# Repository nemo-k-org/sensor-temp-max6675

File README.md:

# Nemo-K temperature sensor for type K thermocouple gauge

## Overview

This is Nemo-K board for ESP-01 and type K thermocouple temperature gauge. The board contains [MAX6675](https://www.analog.com/en/products/max6675.html)
analog-to-digital converter.

Because of its measuring range (0°C to +1024°C) MAX6675 and type K gauge is an ideal setup for measuring components
which may become extremely hot. In boat environment the engine exhaust pipes are typical monitoring target requiring
this type of scale.

The board is designed to be used with ESP-01 microcontroller running Nemo-K firmware.

## Content

The repository contains schematics and PCB in KiCad 8.0 format. The footprint properties contains LCSC part numbers
used by [JLCPBC.com](https://jlcpcb.com). If present, the `sensor-temp-max6675/production/` contains all necessary
files to order boards from JLCPCB. The production files can be easily re-created using
[KiCad Fabrication Toolkit](https://github.com/bennymeg/Fabrication-Toolkit).

The Nemo-K project is not affiliated or sponsored by JLCPCB. The project does not endorse JLCPCB.

## Changelog

* At the moment there is no field tested versions.

## Copyright and License

The license and copyright can be found in the file `LICENSE`.

The license and copyright cover only the schematic diagram and the PCB design. It does not cover footprints and other
embedded elements or technical documentation which may or may not be covered by their own licenses.

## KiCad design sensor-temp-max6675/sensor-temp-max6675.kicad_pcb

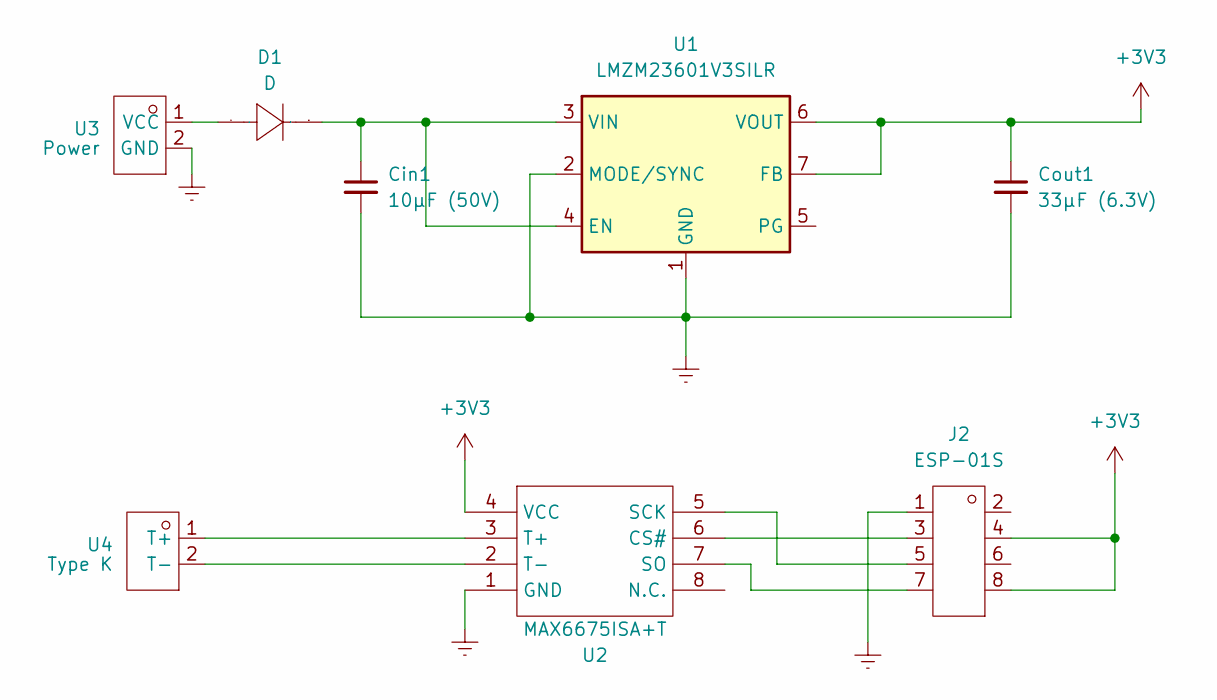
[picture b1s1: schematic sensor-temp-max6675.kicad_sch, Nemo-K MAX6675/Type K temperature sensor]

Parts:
Cin1: 10μF (50V); C_1210_3225Metric; LCSC C2918502
Cout1: 33μF (6.3V); C_1210_3225Metric; Mfg Part C3225X5R1A336MT0A0E; LCSC C531418
D1: D; SOD-323_L1.7-W1.3-LS2.5-RD; Manufacturer Part S7116-300A; LCSC Part Name S7116-300A
J2: ESP-01S; HDR-SMD_8P-P2.54-V-F-R2-C4-S7.1; Mfg Part PM254-2-04-S-8.5; LCSC C3975149
U1: LMZM23601V3SILR; Texas_SIL0010A_MicroSiP-10-1EP_3.8x3mm_P0.6mm_EP0.7x2.9mm_T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; MPN LMZM23601SILR; LCSC C2864948
U2: MAX6675ISA+T; SOIC-8_L5.0-W4.0-P1.27-LS6.0-BL; Manufacturer Part MAX6675ISA+T; LCSC Part Name MAX6675ISA
U3: Power; CONN-TH_MX127S-3.81-02P-GN01-CU-Y-A; Manufacturer Part MX127S-3.81-02P-GN01-Cu-Y-A; LCSC Part Name 1x2P 3.81mm 直插 排数:1 每排P数:2
U4: Type K; CONN-TH_2P-P7.62_KEFA_KF7.62-2P; Manufacturer Part KF7.62-2P(green); LCSC Part Name KF7.62-2P(green) 绿色尼龙环保

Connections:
+3V3: Cout1.1, J2.4 (Ch_PD), J2.8 (+3V3), U1.6 (VOUT), U1.7 (FB), U2.4 (VCC)
Earth: Cin1.2, Cout1.2, J2.1 (Earth), U1.1 (GND), U1.2 (MODE/SYNC), U1.11 (GND), U2.1 (GND), U3.2 (GND)
unnamed: D1.2 (A), U3.1 (VCC)
unnamed: Cin1.1, D1.1 (K), U1.3 (VIN), U1.4 (EN)
unnamed: J2.5 (GPIO0), U2.5 (SCK)
unnamed: J2.3 (GPIO2), U2.6 (CS#)
unnamed: J2.7 (RX/GPIO3), U2.7 (SO)
unnamed: U2.3 (T+), U4.1 (T+)
unnamed: U2.2 (T-), U4.2 (T-)

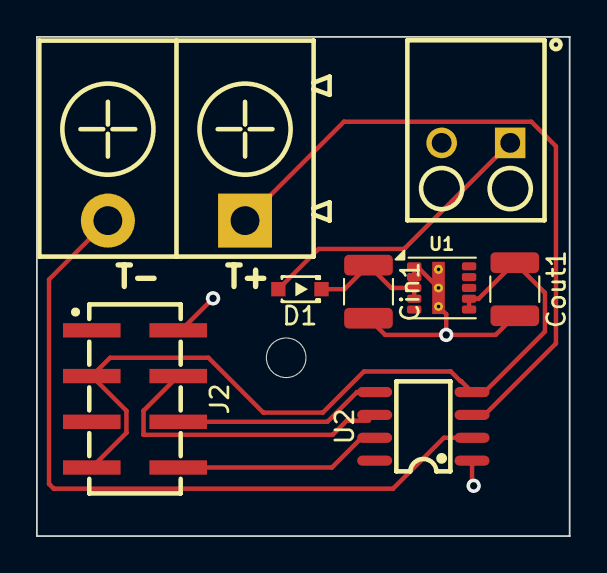
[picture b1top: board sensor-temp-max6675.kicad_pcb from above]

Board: 2 copper layers, 29.6 x 27.7 mm, 8 parts (0 on the bottom side), 9 nets.

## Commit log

2025-01-14 1st UNTESTED version going to production
